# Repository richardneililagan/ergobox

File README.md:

Ergobox: Hitbox-style fightstick
===

> **NOTE: Work in progress.**
>
> This is not yet ready for build.

Ergobox is a low-profile hitbox-style fightstick based off of
[Flatbox rev4][flatbox-rev4].

This project wants to introduce the following changes / adjustments:

- a more ergonomic button layout
- RGB LED lighting
- adjustments to case to allow for easy personalization

while maintaining some key characteristics that make Flatbox great 
in my opinion:

- low-profile build using Kailh switches
- hotswappable switches
- USB-C port 
- no need for an addon board
- compatibility with [RP2040][rp2040] (so we can use, say, [GP2040-CE][gp2040ce] as firmware)
- ready-to-use artifacts for manufacturing

## Credits and thanks

I'd like to express my gratitude to the following projects,
which Ergobox uses as well:

- [Flatbox][flatbox]
- [keyswitch-kicad-library][keyswitch-kicad-library]
- [Type-C.pretty][typec-pretty]
- [CrumpPrints.pretty][crumpprints-pretty]

## License

This project is licensed under GPLv3.
See [LICENSE](./LICENSE) for the full license text.

[flatbox]: https://github.com/jfedor2/flatbox
[flatbox-rev4]: https://github.com/jfedor2/flatbox/tree/master/hardware-rev4
[rp2040]: https://www.raspberrypi.com/documentation/microcontrollers/rp2040.html
[gp2040ce]: https://github.com/OpenStickFoundation/GP2040-CE

[keyswitch-kicad-library]: https://github.com/perigoso/keyswitch-kicad-library
[typec-pretty]: https://github.com/ai03-2725/Type-C.pretty
[crumpprints-pretty]: https://github.com/tylercrumpton/CrumpPrints.pretty

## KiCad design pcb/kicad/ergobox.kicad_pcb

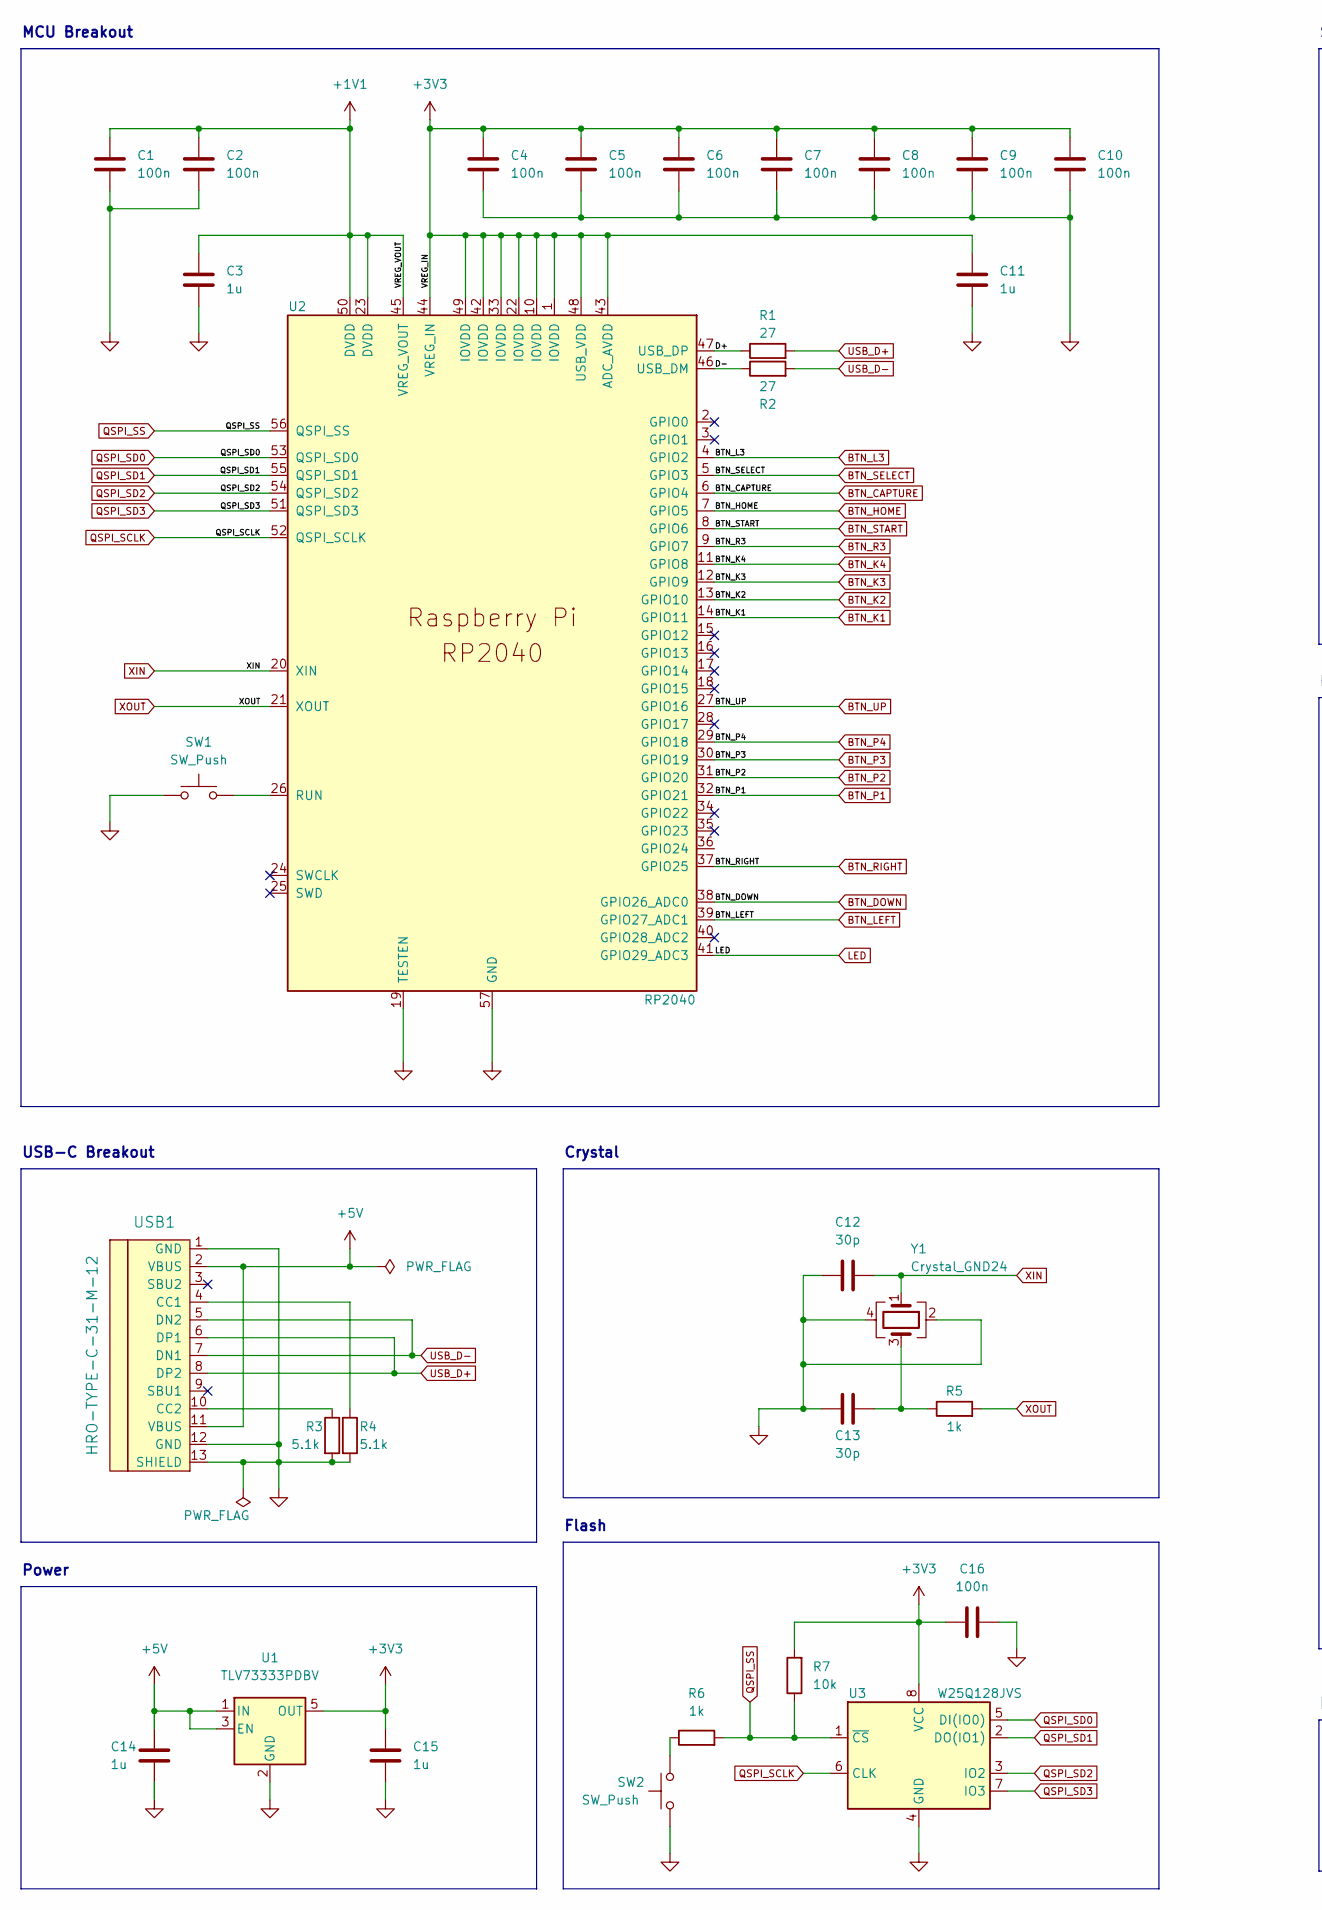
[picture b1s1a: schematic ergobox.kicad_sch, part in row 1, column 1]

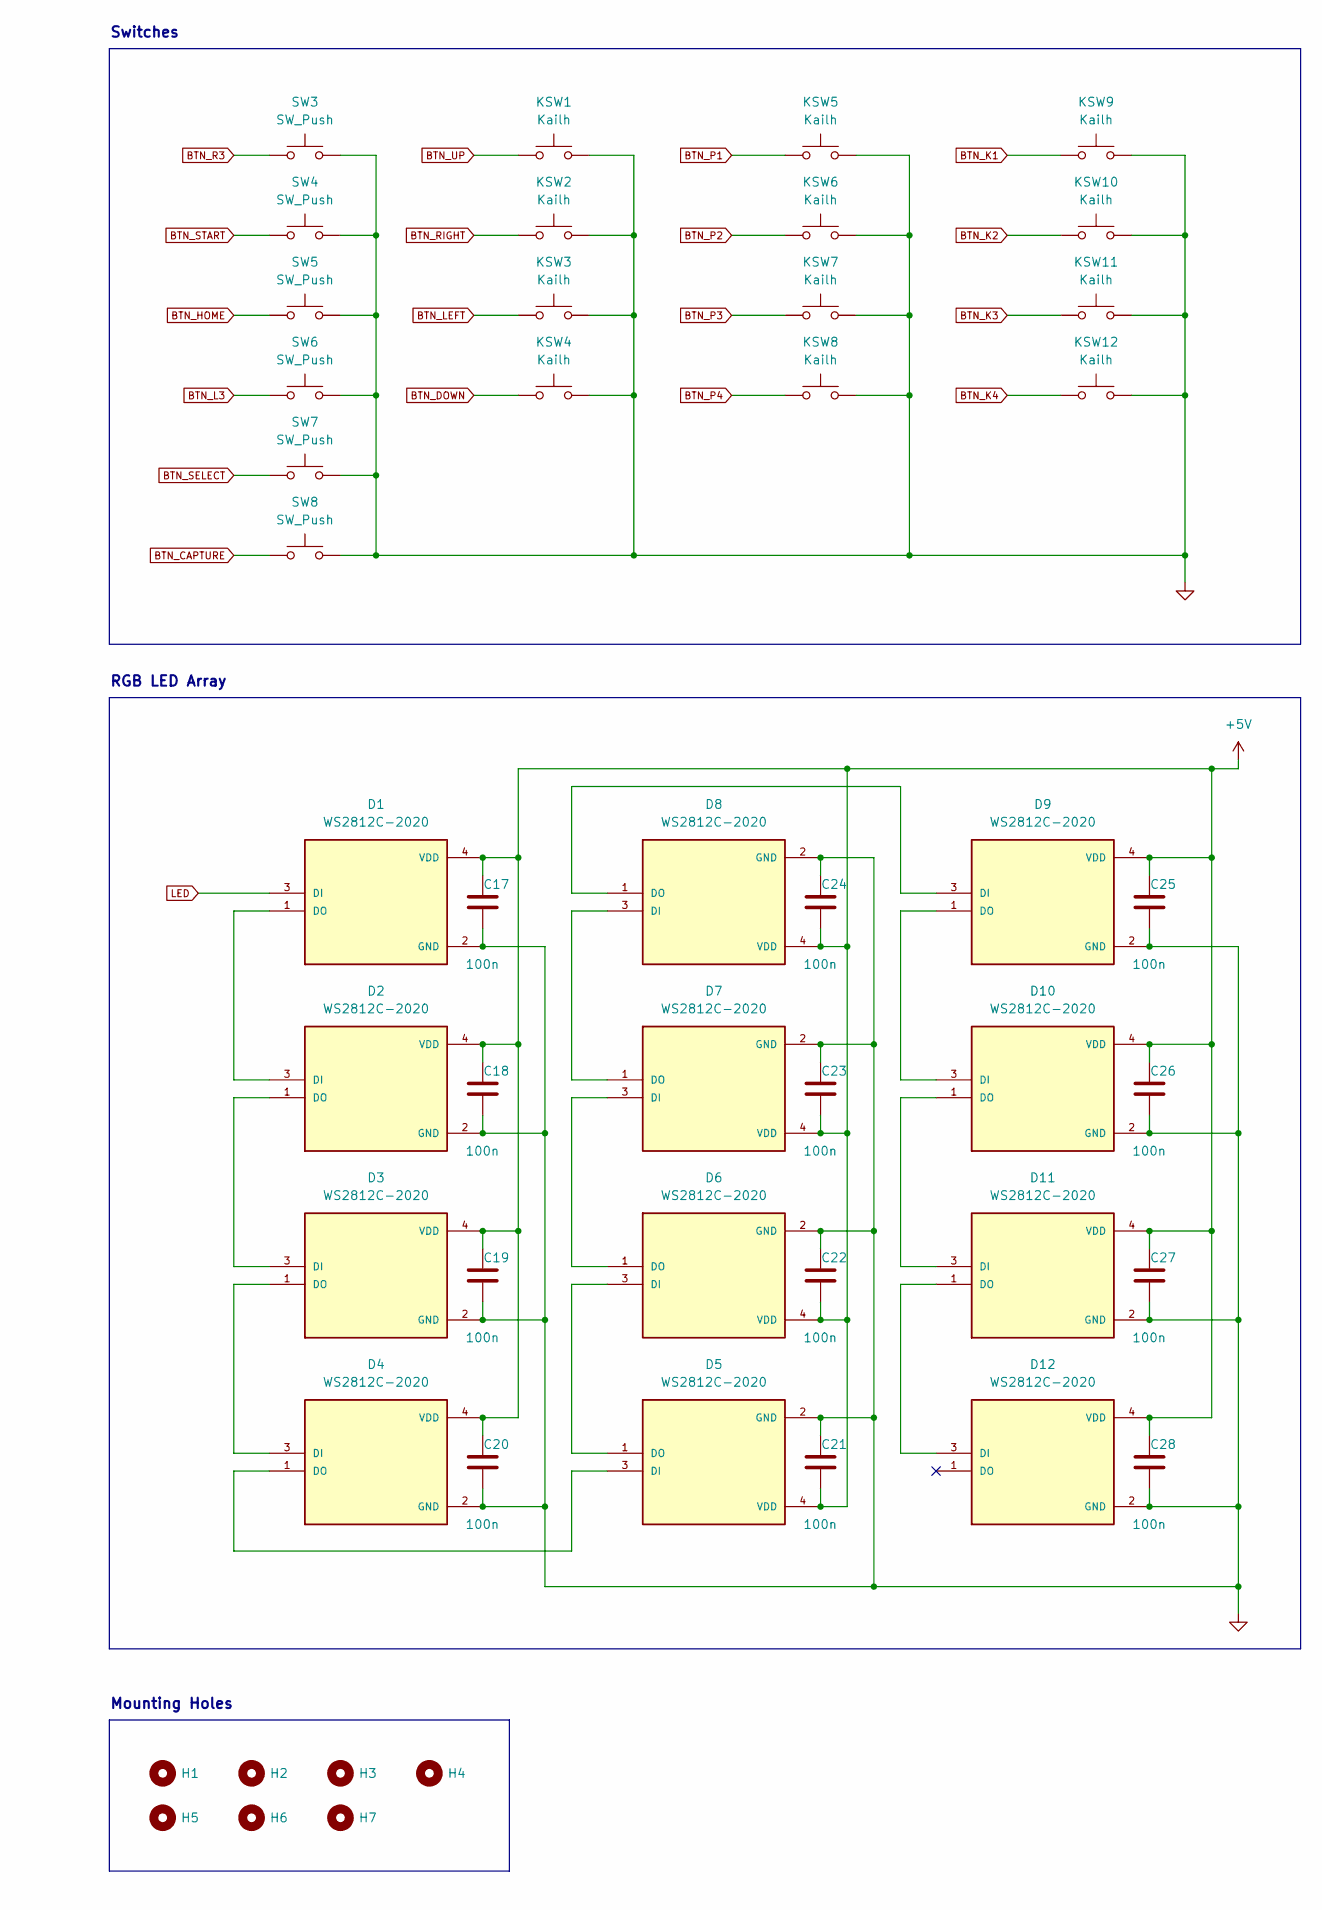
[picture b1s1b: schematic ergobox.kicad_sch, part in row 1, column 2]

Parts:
C1, C2, C4, C5, C6, C7, C8, C9, C10, C16: 100n; C_0402_1005Metric; LCSC C1525
C3, C11, C14, C15: 1u; C_0402_1005Metric; LCSC C52923
C12, C13: 30p; C_0402_1005Metric; LCSC C1570
C17, C18, C19, C20, C21, C22, C23, C24, C25, C26, C27, C28: 100n; C_0402_1005Metric; LCSC C52923
D1, D2, D3, D4, D5, D6, D7, D8, D9, D10, D11, D12: WS2812C-2020; LED_WS2812C-2020; PARTREV V1.0; LCSC C2976072
H1, H2, H3, H4, H5, H6, H7: MountingHole; MountingHole_3.2mm_M3
KSW1, KSW2, KSW3, KSW4, KSW5, KSW6, KSW7, KSW8, KSW9, KSW10, KSW11, KSW12: Kailh; SW_Hotswap_Kailh_Choc_V1V2; JLCPCB_IGNORE true
R1, R2: 27; R_0402_1005Metric; LCSC C138021
R3, R4: 5.1k; R_0402_1005Metric; LCSC C25905
R5, R6: 1k; R_0402_1005Metric; LCSC C11702
R7: 10k; R_0402_1005Metric; LCSC C25744
SW1, SW2: SW_Push; SW_SPST_Omron_B3FS-100xP; LCSC C271750
SW3, SW4, SW5, SW6, SW7, SW8: SW_Push; SW_PUSH_6mm_H5mm; LCSC C620304
U1: TLV73333PDBV; SOT-23-5; LCSC C134139
U2: RP2040; RP2040-QFN-56; LCSC C2040
U3: W25Q128JVS; SOIC-8_5.23x5.23mm_P1.27mm; LCSC C97521
USB1: HRO-TYPE-C-31-M-12; LCSC C165948
Y1: Crystal_GND24; Crystal_SMD_3225-4Pin_3.2x2.5mm; LCSC C9002

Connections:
+1V1: C1.1, C2.1, C3.1, U2.23 (DVDD), U2.45 (VREG_VOUT), U2.50 (DVDD)
+3V3: C4.1, C5.1, C6.1, C7.1, C8.1, C9.1, C10.1, C11.1, C15.1, C16.1, R7.2, U1.5 (OUT), U2.1 (IOVDD), U2.10 (IOVDD), U2.22 (IOVDD), U2.33 (IOVDD), U2.42 (IOVDD), U2.43 (ADC_AVDD), U2.44 (VREG_IN), U2.48 (USB_VDD), U2.49 (IOVDD), U3.8 (VCC)
+5V: C14.1, C17.1, C18.1, C19.1, C20.1, C21.2, C22.2, C23.2, C24.2, C25.1, C26.1, C27.1, C28.1, D1.4 (VDD), D2.4 (VDD), D3.4 (VDD), D4.4 (VDD), D5.4 (VDD), D6.4 (VDD), D7.4 (VDD), D8.4 (VDD), D9.4 (VDD), D10.4 (VDD), D11.4 (VDD), D12.4 (VDD), U1.1 (IN), U1.3 (EN), USB1.2 (VBUS), USB1.11 (VBUS)
/D+: R1.1, U2.47 (USB_DP)
/D-: R2.1, U2.46 (USB_DM)
BTN_CAPTURE: SW8.1, U2.6 (GPIO4)
BTN_DOWN: KSW4.1, U2.38 (GPIO26_ADC0)
BTN_HOME: SW5.1, U2.7 (GPIO5)
BTN_K1: KSW9.1, U2.14 (GPIO11)
BTN_K2: KSW10.1, U2.13 (GPIO10)
BTN_K3: KSW11.1, U2.12 (GPIO9)
BTN_K4: KSW12.1, U2.11 (GPIO8)
BTN_L3: SW6.1, U2.4 (GPIO2)
BTN_LEFT: KSW3.1, U2.39 (GPIO27_ADC1)
BTN_P1: KSW5.1, U2.32 (GPIO21)
BTN_P2: KSW6.1, U2.31 (GPIO20)
BTN_P3: KSW7.1, U2.30 (GPIO19)
BTN_P4: KSW8.1, U2.29 (GPIO18)
BTN_R3: SW3.1, U2.9 (GPIO7)
BTN_RIGHT: KSW2.1, U2.37 (GPIO25)
BTN_SELECT: SW7.1, U2.5 (GPIO3)
BTN_START: SW4.1, U2.8 (GPIO6)
BTN_UP: KSW1.1, U2.27 (GPIO16)
GND: C1.2, C2.2, C3.2, C4.2, C5.2, C6.2, C7.2, C8.2, C9.2, C10.2, C11.2, C12.1, C13.1, C14.2, C15.2, C16.2, C17.2, C18.2, C19.2, C20.2, C21.1, C22.1, C23.1, C24.1, C25.2, C26.2, C27.2, C28.2, D1.2 (GND), D2.2 (GND), D3.2 (GND), D4.2 (GND), D5.2 (GND), D6.2 (GND), D7.2 (GND), D8.2 (GND), D9.2 (GND), D10.2 (GND), D11.2 (GND), D12.2 (GND), KSW1.2, KSW2.2, KSW3.2, KSW4.2, KSW5.2, KSW6.2, KSW7.2, KSW8.2, KSW9.2, KSW10.2, KSW11.2, KSW12.2, R3.2, R4.2, SW1.1, SW2.1, SW3.2, SW4.2, SW5.2, SW6.2, SW7.2, SW8.2, U1.2 (GND), U2.19 (TESTEN), U2.57 (GND), U3.4 (GND), USB1.1 (GND), USB1.12 (GND), USB1.13 (SHIELD), Y1.2, Y1.4
LED: D1.3 (DI), U2.41 (GPIO29_ADC3)
unnamed: C13.2, R5.1, Y1.3
unnamed: D1.1 (DO), D2.3 (DI)
unnamed: D2.1 (DO), D3.3 (DI)
unnamed: D3.1 (DO), D4.3 (DI)
unnamed: D4.1 (DO), D5.3 (DI)
unnamed: D5.1 (DO), D6.3 (DI)
unnamed: D6.1 (DO), D7.3 (DI)
unnamed: D7.1 (DO), D8.3 (DI)
unnamed: D8.1 (DO), D9.3 (DI)
unnamed: D10.1 (DO), D11.3 (DI)
unnamed: D9.1 (DO), D10.3 (DI)
unnamed: D11.1 (DO), D12.3 (DI)
unnamed: R3.1, USB1.10 (CC2)
unnamed: R4.1, USB1.4 (CC1)
unnamed: R6.1, SW2.2
unnamed: SW1.2, U2.26 (RUN)
QSPI_SCLK: U2.52 (QSPI_SCLK), U3.6 (CLK)
QSPI_SD0: U2.53 (QSPI_SD0), U3.5 (DI(IO0))
QSPI_SD1: U2.55 (QSPI_SD1), U3.2 (DO(IO1))
QSPI_SD2: U2.54 (QSPI_SD2), U3.3 (IO2)
QSPI_SD3: U2.51 (QSPI_SD3), U3.7 (IO3)
QSPI_SS: R6.2, R7.1, U2.56 (QSPI_SS), U3.1 (~CS)
USB_D+: R1.2, USB1.6 (DP1), USB1.8 (DP2)
USB_D-: R2.2, USB1.5 (DN2), USB1.7 (DN1)
XIN: C12.2, U2.20 (XIN), Y1.1
XOUT: R5.2, U2.21 (XOUT)

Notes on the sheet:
RGB LED Array
Flash
USB-C Breakout
Mounting Holes
Switches
Power
Crystal
MCU Breakout

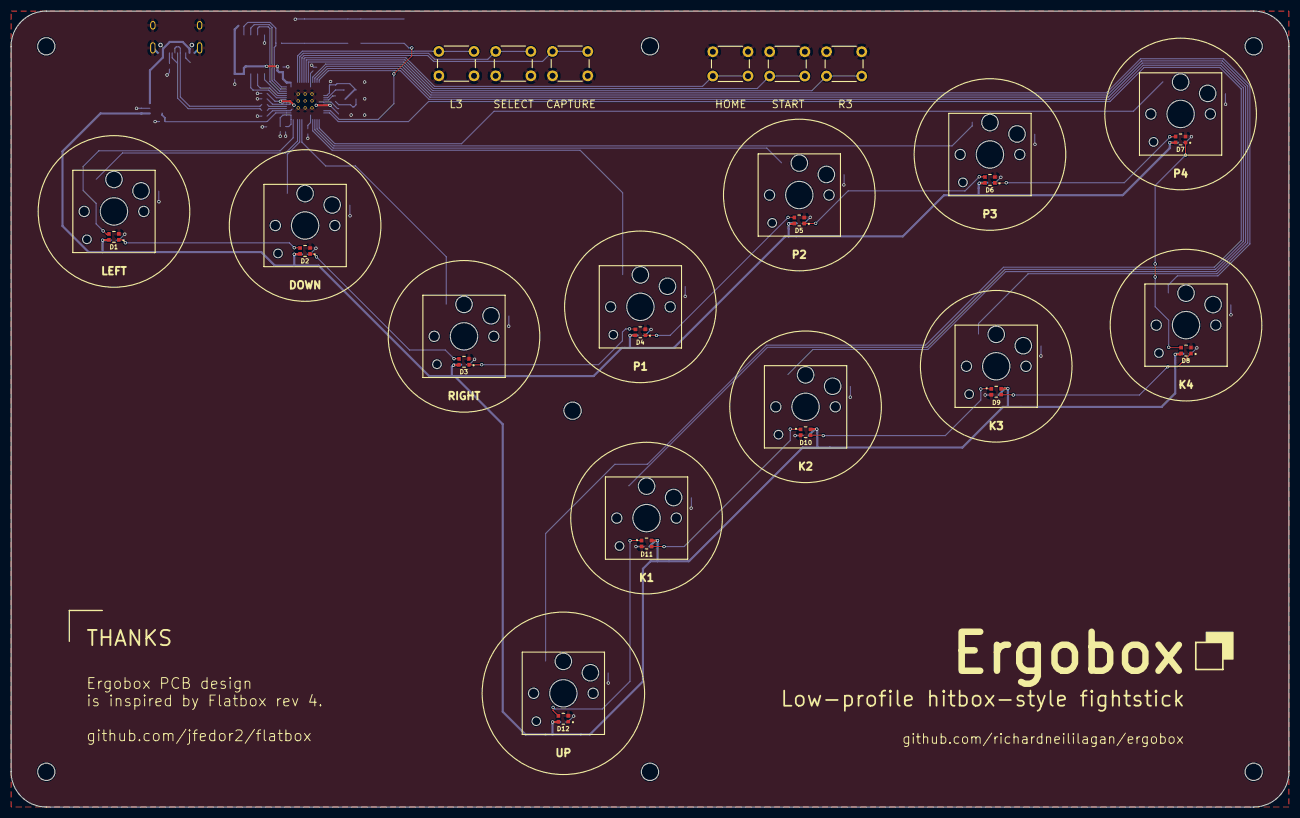
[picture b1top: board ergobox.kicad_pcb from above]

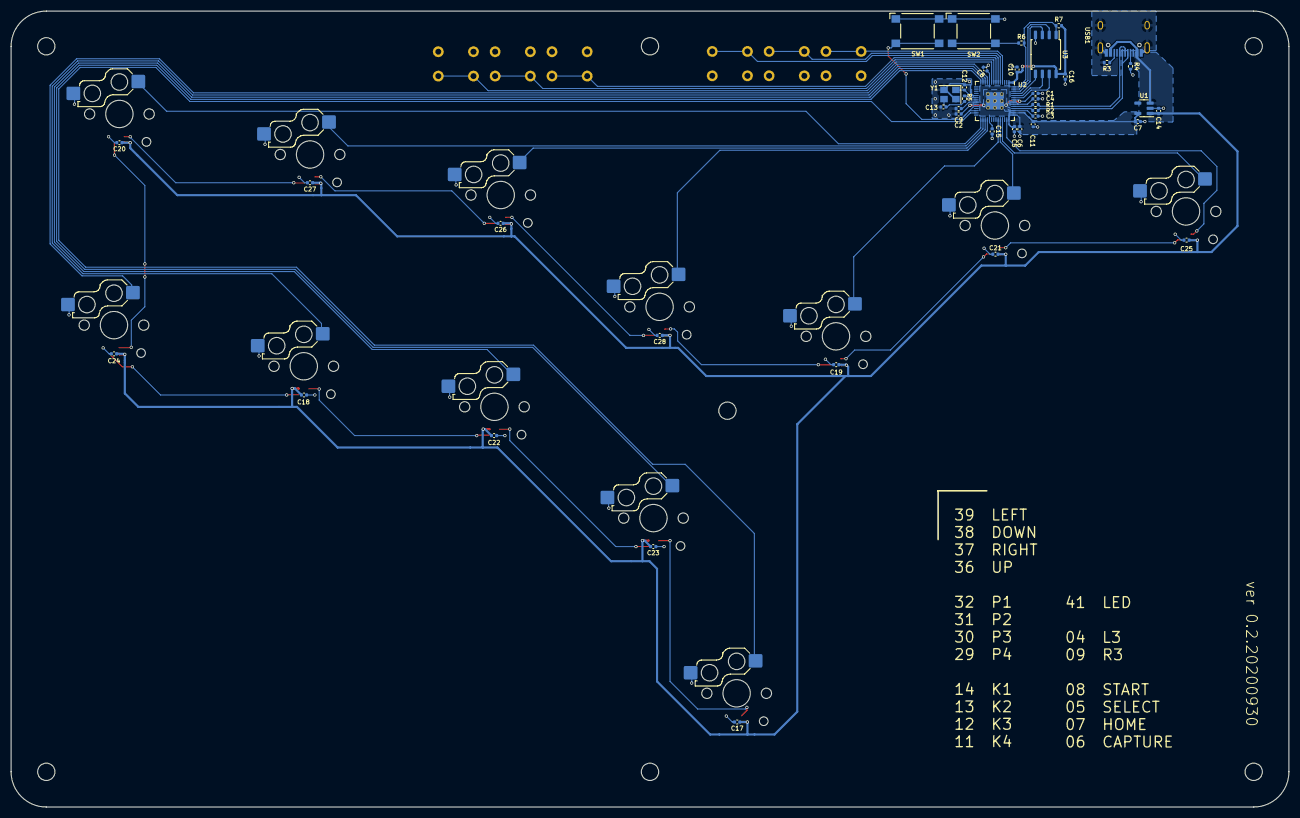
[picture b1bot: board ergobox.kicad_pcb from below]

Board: 2 copper layers, 236.0 x 147.0 mm, 79 parts (42 on the bottom side), 51 nets.

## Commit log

2022-09-23 chore: adds initial includes
2022-09-23 feat: adds initial schematic design
2022-09-23 chore: adds LICENSE and initial README
2022-09-23 feat: updates footprints for Kailh switches and WS2812C-2020
2022-09-23 feat: adds footprints to remaining components
2022-09-23 refactor: changes footprint for Kailh switches to 1350_optional
2022-09-23 feat: adds M4 mounting holes to schematic
2022-09-24 feat: initial PCB setup
2022-09-24 refactor: adjusts initial PCB layout to match viewlix specs
2022-09-25 feat: places kailh switches on PCB
2022-09-25 refactor: changes kailh footprints to hotswap non-optionals.
    The kailh low footprints with optional hotswaps are not symmetric.
    In the optional footprint, the hotswap switch pad goes through the RGB footpad,
    so it cannot be used.
2022-09-25 feat: places per-key RGB LEDs on PCB
2022-09-25 feat: introduces GND plane on B.Cu
2022-09-25 feat: checkin milestone
2022-09-26 feat: initial lay out for flash and power
2022-09-26 feat: adds +3V3 copper fill in RP2040 footprint
2022-09-26 fix: adjusts copper fills
2022-09-26 feat: initial completed PCB layout
2022-09-26 chore: adjusts aesthetics
2022-09-26 feat: adds Omron B3FS-1000P CAD model
2022-09-26 feat: adds USB-C port CAD model
2022-09-26 feat: adds RP2040 and Kailh switch CAD models
2022-09-26 fix: corrects 3d model for SOIC flash
2022-09-27 refactor: adjusts design to grid origin
2022-09-27 refactor: updates PCB model to use STEP models instead of WRL
2022-09-30 refactor: creates Ergobox v0.2 PCB design, with most SMD components on the underside
2022-09-30 chore: adds silkscreen boundaries for circular arcade buttons
2022-09-30 chore: adds silkscreen labels for aux buttons
2022-09-30 chore: adds GPIO pin numbers for button assignments to B.Silkscreen
2022-09-30 fix: adds LED data GPIO pin to B.Silkscreen legend
2022-09-30 chore: adds aesthetic elements to PCB design
2022-09-30 chore: adds fab output to gitignore
2022-09-30 chore: adds JLCPCB part numbers to symbol fields
2022-09-30 chore: adjusts schematic and PCB metadata for BOM/POS export
2022-10-01 chore: adds exclusions for courtyard violations
2022-10-01 chore: adds make command for generating pcb fab artifacts
2022-10-01 chore: prep for 3d modeling
2025-05-06 chore: adds kicad project
